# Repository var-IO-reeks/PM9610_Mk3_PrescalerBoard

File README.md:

# PM9610_Mk3_PrescalerBoard

This is a fork of SaabFANs original "PM9160_Mk3_PrescalerBoard"-Project. I fixed some minor KiCad-Related Layout issues, cleaned up the schematic a little bit to improve readability and made the Board compatible with Aislers "Beautiful Boards Budget Simple" PCB manufacturing service.

This is a recreation of the PM9160 Prescaler-Board, used in the PM6654x Programmable Counters made by Philips back in the late 80s / early 90s. 
It divides incoming frequencies by 16. With this, a 2.4 Ghz Signal can be counted by the "Counter on a Chip"-Hardware inside the Counter, to which the signal is routed internally on the Mainboard. 

The board uses modern ICs to recreate the original function of the board, which makes it possible to put everything inside the 10x10cm Limit for a cheap 2 Layer Board from most board manufacturers. 
An AtTiny1616 Processor replaces the original analog circuit for the detection of an RF Signal Present and for the handling of Signals !B and TEST_GO. For better Accessibility during testing, the component side has been changed from the original Board. 
Software for the AtTiny1616 is written in C with the PlatformIO-IDE. 

Note: It might be necessary to use longer Pin Headers for the connectors. Make sure, the pins are not too long though, as they can touch the case and short out the 5V and -8.5V Rails!

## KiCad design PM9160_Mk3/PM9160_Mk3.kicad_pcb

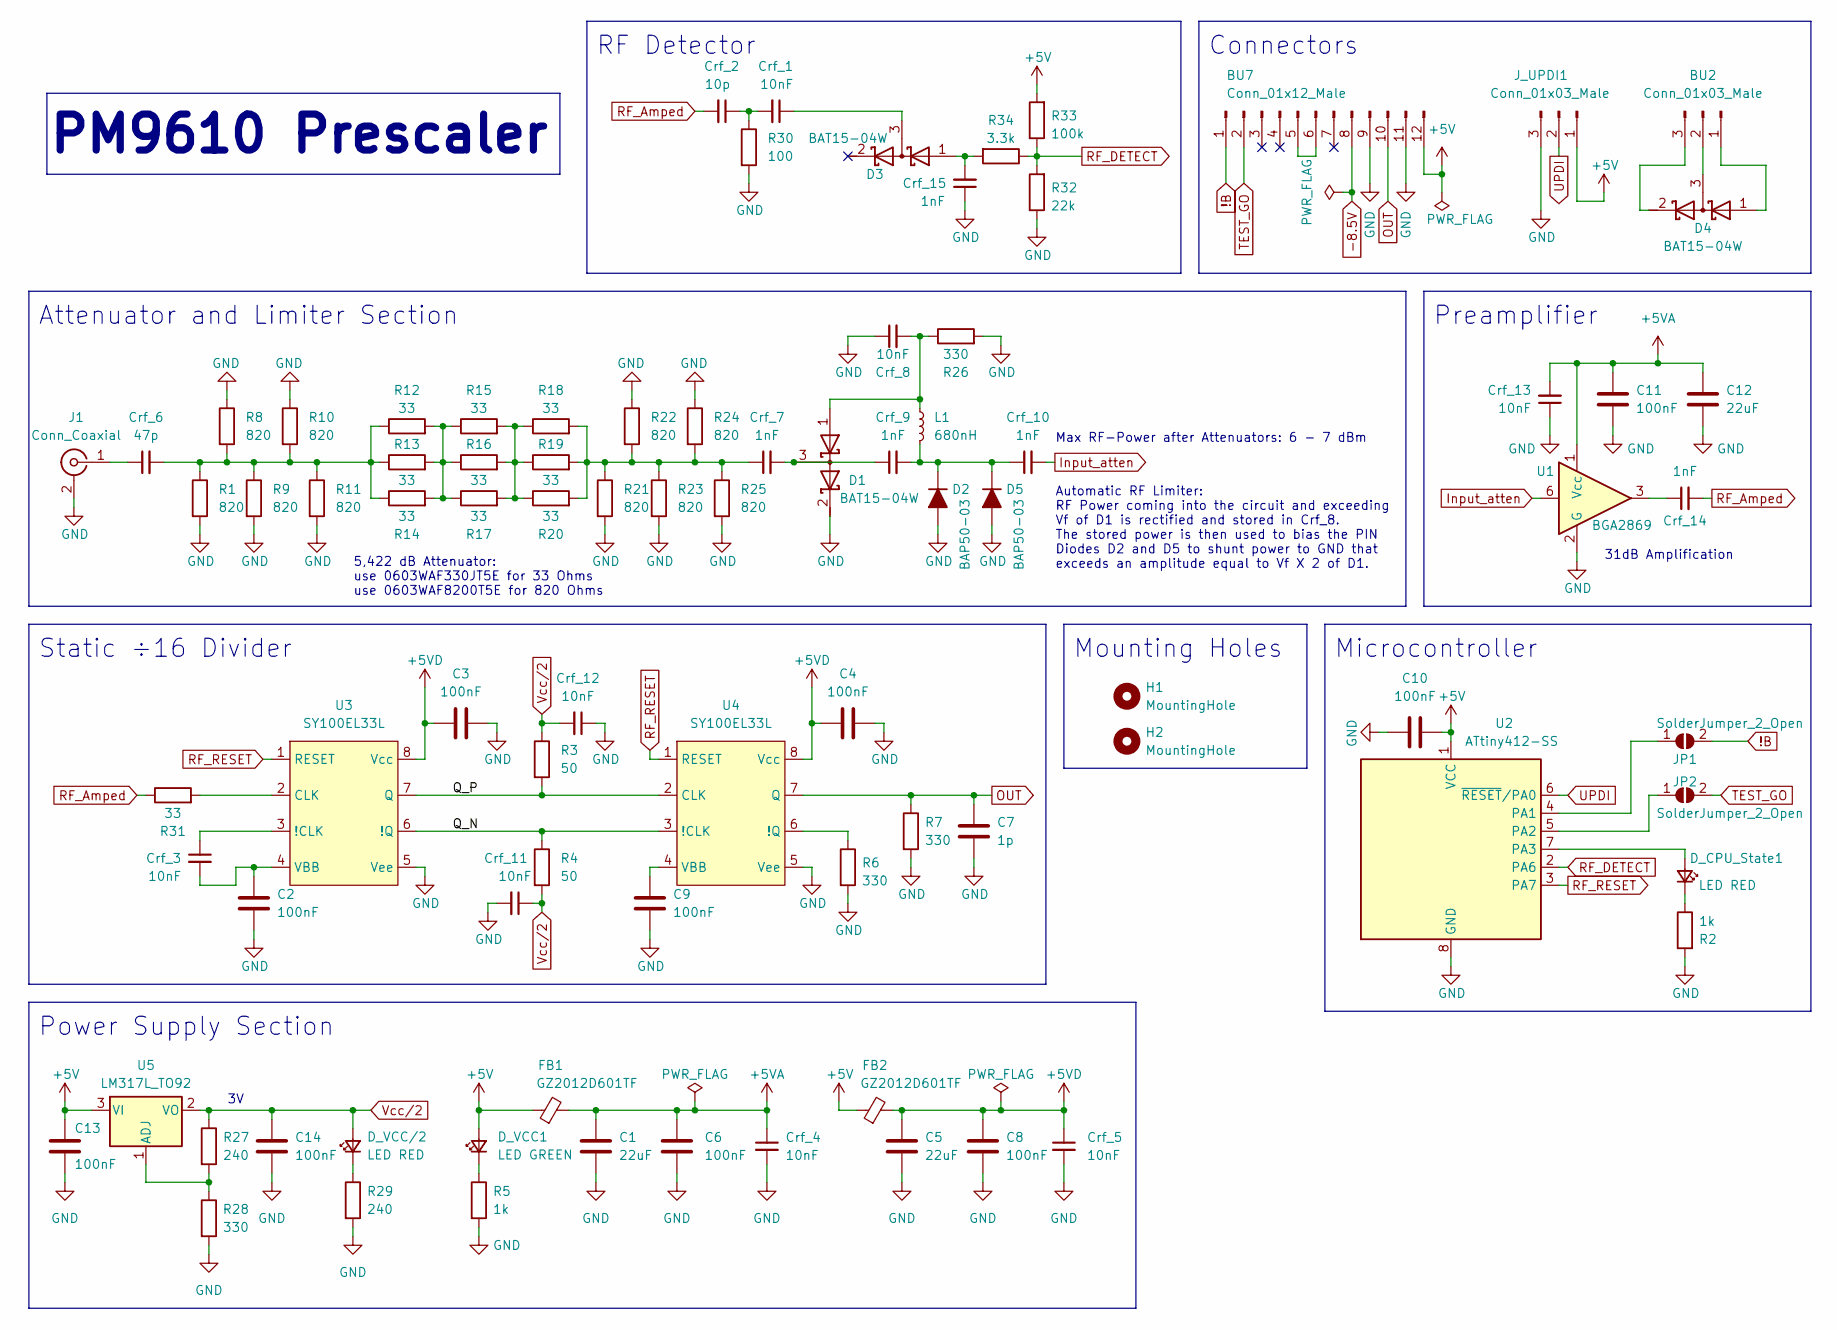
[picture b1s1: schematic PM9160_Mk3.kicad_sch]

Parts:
BU2: Conn_01x03_Male; PinHeader_1x03_P2.54mm_Vertical
BU7: Conn_01x12_Male; PinHeader_1x12_P2.54mm_Horizontal
C1, C5, C12: 22uF; C_0603_1608Metric
C2, C3, C4, C6, C8, C9, C10, C11, C13, C14: 100nF; C_0603_1608Metric
C7: 1p; C_0603_1608Metric
Crf_1, Crf_3, Crf_4, Crf_5, Crf_8, Crf_11, Crf_12, Crf_13: 10nF; C_0402_1005Metric
Crf_2: 10p; C_0402_1005Metric
Crf_6: 47p; C_0402_1005Metric
Crf_7, Crf_9, Crf_10, Crf_14, Crf_15: 1nF; C_0402_1005Metric
D1, D3, D4: BAT15-04W; SOT-323_SC-70
D2, D5: BAP50-03; D_SOD-323_HandSoldering
D_CPU_State1: LED RED; LED_0603_1608Metric
D_VCC1: LED GREEN; LED_0603_1608Metric
D_VCC/2: LED RED; LED_0603_1608Metric
FB1, FB2: GZ2012D601TF; L_0805_2012Metric
H1, H2: MountingHole; MountingHole_3.2mm_M3_DIN965
J1: Conn_Coaxial; SMA_Molex_73251-1153_EdgeMount_Horizontal
JP1, JP2: SolderJumper_2_Open; SolderJumper-2_P1.3mm_Open_TrianglePad1.0x1.5mm
J_UPDI1: Conn_01x03_Male; PinHeader_1x03_P2.54mm_Vertical
L1: 680nH; L_0603_1608Metric
R1, R8, R9, R10, R11, R21, R22, R23, R24, R25: 820; R_0603_1608Metric
R2, R5: 1k; R_0603_1608Metric
R3, R4: 50; R_0603_1608Metric
R6, R7, R26, R28: 330; R_0603_1608Metric
R12, R13, R14, R15, R16, R17, R18, R19, R20, R31: 33; R_0603_1608Metric
R27, R29: 240; R_0603_1608Metric
R30: 100; R_0603_1608Metric
R32: 22k; R_0603_1608Metric
R33: 100k; R_0603_1608Metric
R34: 3.3k; R_0603_1608Metric
U1: BGA2869; SOT-363_SC-70-6
U2: ATtiny412-SS; SOIC-8_3.9x4.9mm_P1.27mm
U3, U4: SY100EL33L; SOIC-8_3.9x4.9mm_P1.27mm
U5: LM317L_TO92; TO-92_Inline

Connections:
!B: BU7.1, JP1.2 (B)
+5V: BU7.12, C10.2, C13.1, D_VCC1.2 (A), FB1.1, FB2.1, J_UPDI1.1, R33.2, U2.1 (VCC), U5.3 (VI)
+5VA: C1.1, C6.1, C11.2, C12.1, Crf_4.1, Crf_13.2, FB1.2, U1.1 (Vcc)
+5VD: C3.1, C4.1, C5.1, C8.1, Crf_5.1, FB2.2, U3.8 (Vcc), U4.8 (Vcc)
-8.5V: BU7.8
/Q_N: R4.1, U3.6 (!Q), U4.3 (!CLK)
/Q_P: R3.2, U3.7 (Q), U4.2 (CLK)
GND: BU7.9, BU7.11, C1.2, C2.2, C3.2, C4.2, C5.2, C6.2, C7.2, C8.2, C9.2, C10.1, C11.1, C12.2, C13.2, C14.2, Crf_4.2, Crf_5.2, Crf_8.1, Crf_11.2, Crf_12.1, Crf_13.1, Crf_15.1, D1.2 (K), D2.2 (A), D5.2 (A), J1.2 (Ext), J_UPDI1.3, R1.2, R2.2, R5.2, R6.2, R7.2, R8.1, R9.2, R10.1, R11.2, R21.2, R22.1, R23.2, R24.1, R25.2, R26.2, R28.2, R29.2, R30.2, R32.1, U1.2 (G), U1.4 (G), U1.5 (G), U2.8 (GND), U3.5 (Vee), U4.5 (Vee)
Input_atten: Crf_10.2, U1.6
unnamed: BU2.1, D4.1 (A)
unnamed: BU2.2, D4.3 (common)
unnamed: BU2.3, D4.2 (K)
unnamed: BU7.5, BU7.6
unnamed: Crf_1.2, Crf_2.1, R30.1
unnamed: Crf_6.2, R1.1, R8.2, R9.1, R10.2, R11.1, R12.1, R13.1, R14.1
unnamed: Crf_7.1, R18.2, R19.2, R20.2, R21.1, R22.2, R23.1, R24.2, R25.1
unnamed: Crf_14.1, U1.3
unnamed: Crf_8.2, D1.1 (A), L1.1, R26.1
unnamed: Crf_7.2, Crf_9.1, D1.3 (common)
unnamed: Crf_9.2, Crf_10.1, D2.1 (K), D5.1 (K), L1.2
unnamed: Crf_15.2, D3.1 (A), R34.2
unnamed: Crf_1.1, D3.3 (common)
unnamed: D_CPU_State1.2 (A), U2.7 (PA3)
unnamed: D_CPU_State1.1 (K), R2.1
unnamed: D_VCC1.1 (K), R5.1
unnamed: D_VCC/2.1 (K), R29.1
unnamed: Crf_6.1, J1.1 (In)
unnamed: JP1.1 (A), U2.4 (PA1)
unnamed: JP2.1 (A), U2.5 (PA2)
unnamed: R12.2, R13.2, R14.2, R15.1, R16.1, R17.1
unnamed: R15.2, R16.2, R17.2, R18.1, R19.1, R20.1
unnamed: Crf_3.1, U3.3 (!CLK)
unnamed: R31.2, U3.2 (CLK)
unnamed: C2.1, Crf_3.2, U3.4 (VBB)
unnamed: R6.1, U4.6 (!Q)
unnamed: C9.1, U4.4 (VBB)
unnamed: R27.2, R28.1, U5.1 (ADJ)
OUT: BU7.10, C7.1, R7.1, U4.7 (Q)
RF_Amped: Crf_2.2, Crf_14.2, R31.1
RF_DETECT: R32.2, R33.1, R34.1, U2.2 (PA6)
RF_RESET: U2.3 (PA7), U3.1 (RESET), U4.1 (RESET)
TEST_GO: BU7.2, JP2.2 (B)
UPDI: J_UPDI1.2, U2.6 (~RESET/PA0)
Vcc/2: C14.1, Crf_11.1, Crf_12.2, D_VCC/2.2 (A), R3.1, R4.2, R27.1, U5.2 (VO)

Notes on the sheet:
Power Supply Section
PM9610 Prescaler
Automatic RF Limiter: RF Power coming into the circuit and exceeding Vf of D1 is rectified and stored in Crf_8. The stored power is then used to bias the PIN Diodes D2 and D5 to shunt power to GND that exceeds an amplitude equal to Vf X 2 of D1.
Max RF-Power after Attenuators: 6 - 7 dBm
Microcontroller
RF Detector
Static ÷16 Divider
5,422 dB Attenuator: use 0603WAF330JT5E for 33 Ohms use 0603WAF8200T5E for 820 Ohms
Preamplifier
Connectors
Mounting Holes
Attenuator and Limiter Section
31dB Amplification

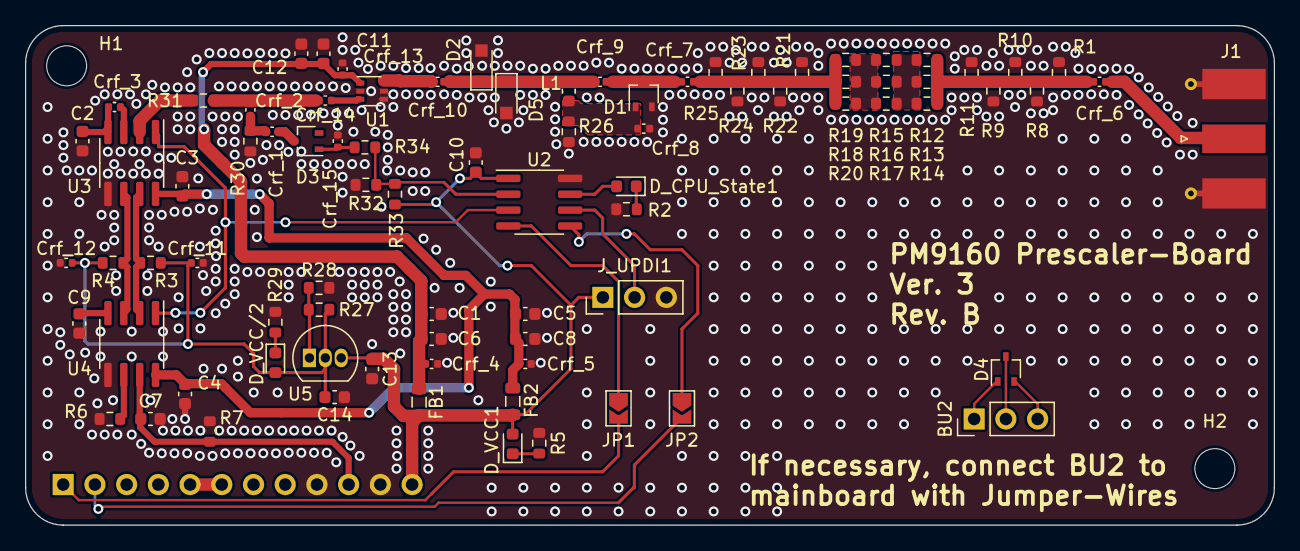
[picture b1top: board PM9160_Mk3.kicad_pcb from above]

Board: 2 copper layers, 100.0 x 40.0 mm, 87 parts (1 on the bottom side), 43 nets.

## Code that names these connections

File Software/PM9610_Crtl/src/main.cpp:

#include <Arduino.h>

// Pin-Definitions
#define RF_DETECT PIN_PA1
#define RF_RESET PIN_PA2
#define B PIN_PA3
#define CPU_STATE PIN_PA6
#define TEST_GO PIN_PA7

#define RF_THRESHOLD 500  // Threshold Voltage at which RF-Signal is strong enough to be reliably detected by the Divider-Chips
#define ADC_VREF 2500.0  // Internal Reference Voltage of the ADC in mV

float voltRead(uint8_t pin);

void setup() {
  // put your setup code here, to run once:
  pinMode(RF_DETECT, INPUT);
  pinMode(RF_RESET, OUTPUT);
  pinMode(B, INPUT_PULLUP);
  pinMode(CPU_STATE, OUTPUT);
  pinMode(TEST_GO, INPUT_PULLUP);
  digitalWrite(RF_RESET, HIGH);
  digitalWrite(CPU_STATE, LOW);
  if(ADC_VREF < 5000){
    analogReference(INTERNAL2V5);
  } else {
    analogReference(INTERNAL4V3);
  }
}

void loop() {
  // put your main code here, to run repeatedly:
  if(voltRead(RF_DETECT) > RF_THRESHOLD){
    digitalWrite(CPU_STATE, HIGH);
  } else {
    digitalWrite(CPU_STATE, LOW);
  }
}

/*
  @brief Read voltage from a pin by using the analogRead-Function to get raw ADC Value and then convert it to a voltage value.
  @param pin: Pin to read voltage from
  @return Voltage in mV
*/
float voltRead(uint8_t pin) {
  return (ADC0_RES * ADC_VREF) / 1023.0;
}

// TODO: Setup Timers for timer-based check of the RF-Detect-Pin
// TODO: ISR for the Timer Interrupt based approach
// TODO: Implement the RF-Reset-Functionality

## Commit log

2023-08-04 Added KiCAD Files and the ATSTART-File for configuring the Mikrocontroller.
2024-02-12 Minor Changes to PCB layout, cleaned up schematic, fixed some DRC/ERC errors and warnings, made board compatible with Aislers "simple" PCB Service
2024-02-18 changed microcontroller to SOIC-8 Attiny412 for easier handsoldering.
2024-02-19 Changed resistor-footprints of the capacitors to proper capacitor footprints.
2024-02-19 Manual sync with upsteam Software changes.
